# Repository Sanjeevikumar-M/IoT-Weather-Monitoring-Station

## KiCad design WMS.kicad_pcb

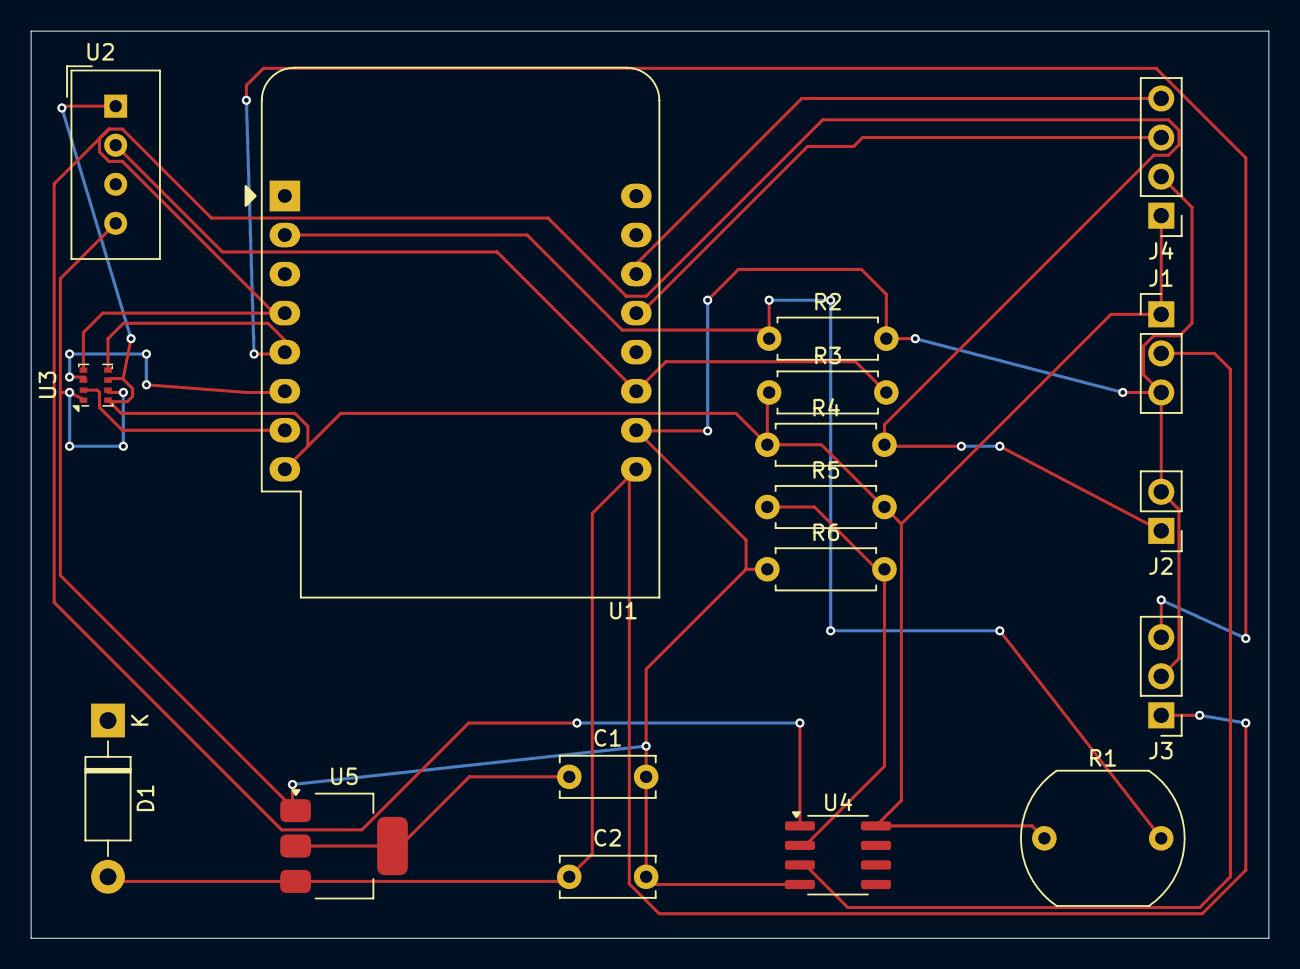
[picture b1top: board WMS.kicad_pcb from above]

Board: 2 copper layers, 80.5 x 59.0 mm, 18 parts (0 on the bottom side), 14 nets.

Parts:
C1, C2: 10uF; C_Disc_D6.0mm_W2.5mm_P5.00mm
D1: 1N4007; D_DO-41_SOD81_P10.16mm_Horizontal
J1, J3: Conn_01x03; PinHeader_1x03_P2.54mm_Vertical
J2: Conn_01x02; PinHeader_1x02_P2.54mm_Vertical
J4: Conn_01x04; PinHeader_1x04_P2.54mm_Vertical
R1: LDR03; R_LDR_10x8.5mm_P7.6mm_Vertical
R2, R4, R5, R6: 10k; R_Axial_DIN0207_L6.3mm_D2.5mm_P7.62mm_Horizontal
R3: 4.7k; R_Axial_DIN0207_L6.3mm_D2.5mm_P7.62mm_Horizontal
U1: WEMOS_D1_mini; WEMOS_D1_mini_light
U2: DHT11; Aosong_DHT11_5.5x12.0_P2.54mm
U3: BMP280; Bosch_LGA-8_2x2.5mm_P0.65mm_ClockwisePinNumbering
U4: LM393; SOIC-8_3.9x4.9mm_P1.27mm
U5: AMS1117-3.3; SOT-223-3_TabPin2

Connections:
/3V3: J1.1, J4.1, R1.1, R3.1, R4.1, R5.2, U1.8 (3V3), U2.1 (VDD), U3.6 (VDDIO), U3.8 (VDD), U4.8 (V+)
/5V: C2.1, D1.2 (A), J3.1, U1.9 (5V), U5.3 (VI)
/A0: R1.2, R2.1, U1.2 (A0)
/D1: J4.4, U1.14 (SCL/D1)
/D2: J4.3, U1.13 (SDA/D2)
/D4: R3.2, U1.11 (D4), U2.2 (DATA)
/D5: J2.1, R4.2, U1.4 (SCK/D5), U3.4 (SCK), U4.1
/D6: J3.3, U1.5 (MISO/D6), U3.5 (SDO)
/D7: U1.6 (MOSI/D7), U3.3 (SDI)
/D8: U1.7 (CS/D8), U3.2 (CSB)
GND: C1.2, C2.2, J1.3, J2.2, J3.2, J4.2, R2.2, R6.1, U1.10 (GND), U2.4 (GND), U3.1 (GND), U3.7 (GND), U4.4 (V-), U5.1 (GND)
unnamed: J1.2, U4.3 (+)
unnamed: R5.1, R6.2, U4.2 (-)
unnamed: C1.1, U5.2 (VO)

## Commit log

2025-03-30 New Update
2025-04-01 Updated PCB
